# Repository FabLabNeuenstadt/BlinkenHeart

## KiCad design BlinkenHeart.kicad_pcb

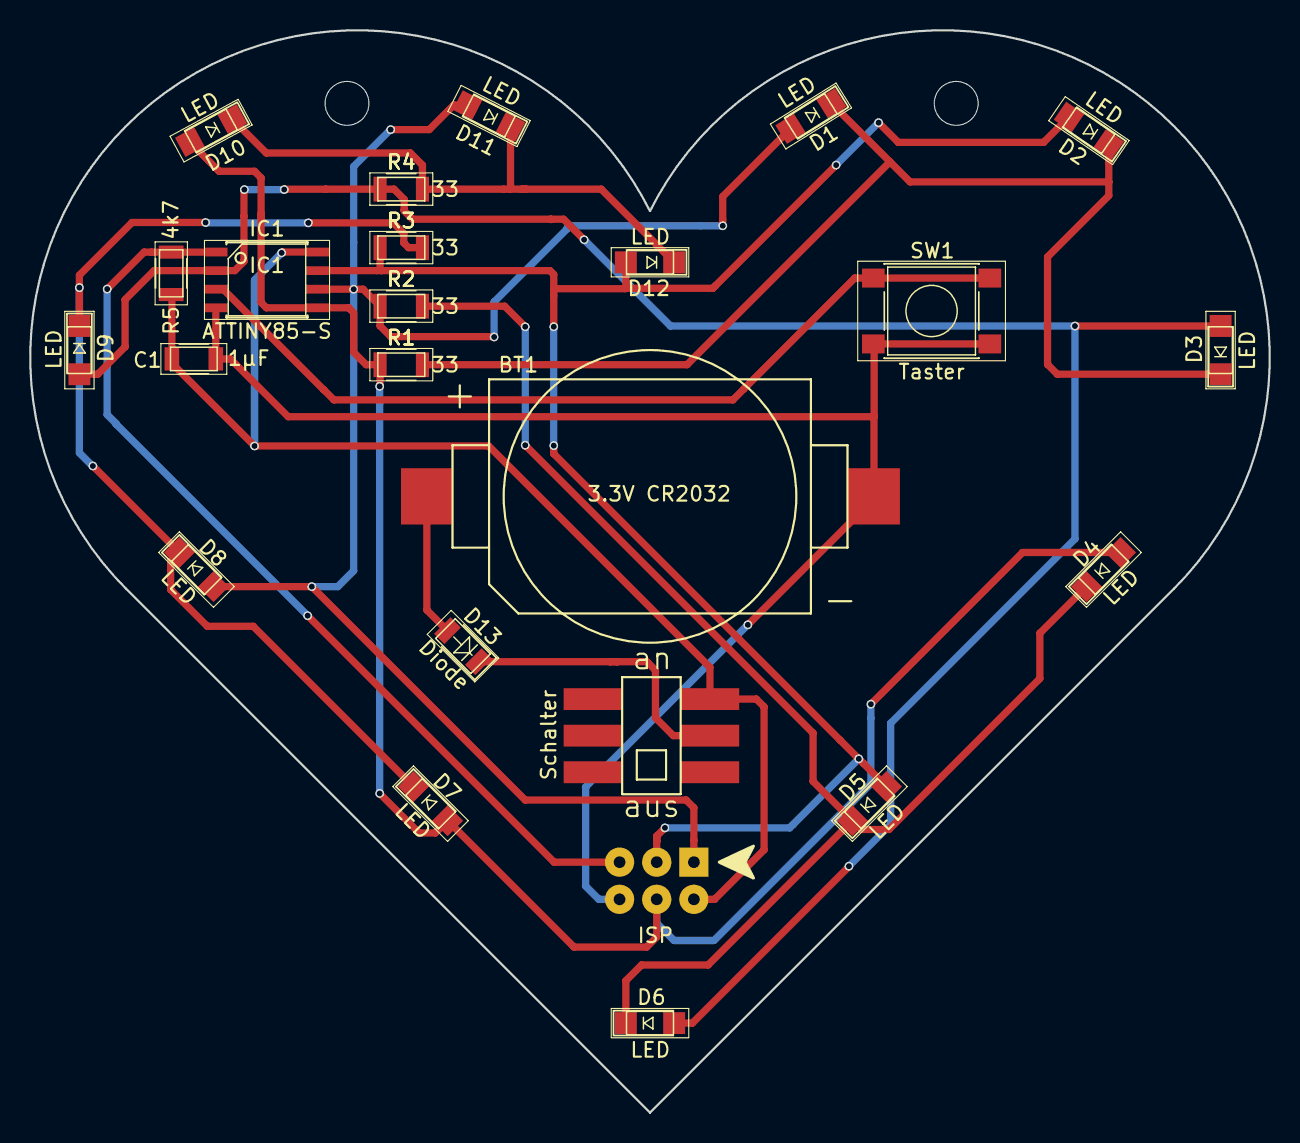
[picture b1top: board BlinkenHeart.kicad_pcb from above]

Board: 2 copper layers, 84.7 x 74.0 mm, 24 parts (0 on the bottom side), 14 nets.

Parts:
BT1: 3.3V CR2032; CR2032-Holder
C1: 1μF; C_1206
D1, D2, D3, D4, D5, D6, D7, D8, D9, D10, D11, D12: LED; LED_1206
D13: D13; D_1206
IC1: ATTINY85-S; SOIC-8_3.9x4.9mm_Pitch1.27mm
ICSP1: ISP; isp_pogo
R1, R2, R3, R4: 33; R_1206
R5: 4k7; R_1206
SW1: Taster; SW_SPST_PTS645
SW2: Schalter; Soerens_Wunderschalter

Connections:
1: D4.2, D7.2, D10.2, IC1.5, ICSP1.4, R1.1
2: D1.2, D8.2, D11.2, IC1.6, ICSP1.1, R2.1
3: D2.2, D5.2, D12.2, IC1.7, ICSP1.3, R3.1
4: D3.2, D6.2, D9.2, IC1.2, R4.1
GND: BT1.2, C1.2, IC1.4, ICSP1.6, SW1.1
unnamed: BT1.1, D13.2
unnamed: D1.1, D2.1, D3.1, R1.2
unnamed: D4.1, D5.1, D6.1, R2.2
unnamed: D7.1, D8.1, D9.1, R3.2
unnamed: D10.1, D11.1, D12.1, R4.2
unnamed: D13.1, SW2.2
unnamed: IC1.3, SW1.2
RST: IC1.1, ICSP1.5, R5.1
VCC: C1.1, IC1.8, ICSP1.2, R5.2, SW2.3

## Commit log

2017-03-05 :lollipop: Added .gitattributes
2017-03-05 First Upload
    Crashkurs mit Jan
2017-03-14 Did some refactoring of the schematic. Ordered the ICSP Pins. Added a VCC Capacitor and an Reset-Pull-Up-Resisor
2017-04-06 assigned missing footprints
2017-04-06 finished border-cuts and routing
    border-cuts is now a mathematicaly correct defined heart (thanks Mathias)
    routing is complete, but needs some aesthetic changes
2017-04-07 fixed ground-connection to battery-holder and made some aesthethik changes to the routing
2017-04-07 added fablab-neuenstadt logo
2017-04-07 moved net 3 away from ground-pin of the battery-holder
2017-04-09 Fixed the ICSP Header
2017-05-06 Fixed the Attiny footprint
2017-05-14 Added some holes, fixed some other minor things. Also: Added a logo and did some rerouting
2017-05-16 Next prototype version blah blah blah
2017-06-20 Did some rerouting
2017-07-21 Some rerouting (by Carsten)
2017-07-30 Merged the Silkscreen layers and removed some unused Components. Did some rotations and added the export.zip to .gitignore
2017-07-31 added border of on/off-Switch to Silkscreen
2017-07-31 Changed the position of an
2017-08-04 Final rotation
2017-08-04 Added a automatic build script (for the gerber files) for linux
2017-08-04 Added drill support and fixed some issues
2017-08-04 Fixed an issue with dirtyPcb (i should do some cleanups now)
